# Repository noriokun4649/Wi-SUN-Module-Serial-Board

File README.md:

# Wi-SUN-Module-Serial-Board
秋月電子の謎SoCに内蔵されている Wi-SUN モジュール MB-RL7023-11 をUSBシリアルに変換する基板です。

# 基板画像

# 回路図

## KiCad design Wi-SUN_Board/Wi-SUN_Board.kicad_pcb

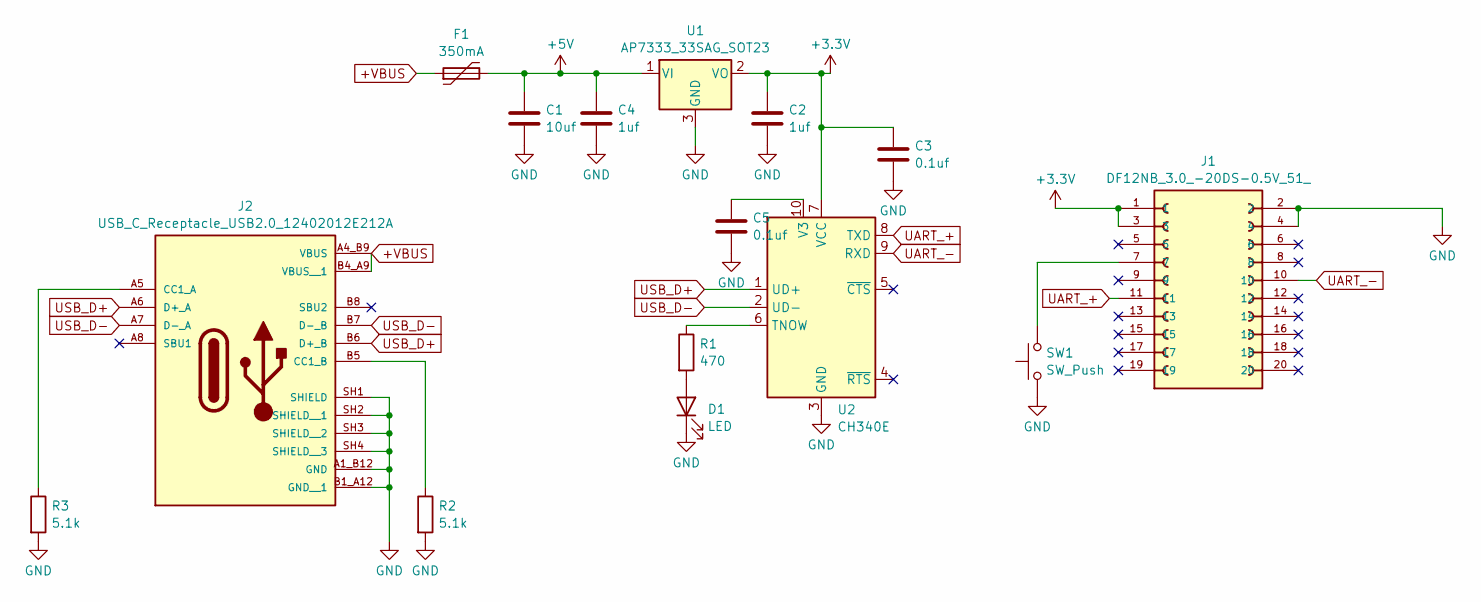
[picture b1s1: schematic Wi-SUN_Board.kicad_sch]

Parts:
C1: 10uf; C_0603_1608Metric_Pad1.08x0.95mm_HandSolder
C2, C4: 1uf; C_0402_1005Metric_Pad0.74x0.62mm_HandSolder
C3, C5: 0.1uf; C_0402_1005Metric_Pad0.74x0.62mm_HandSolder
D1: LED; LED_0603_1608Metric_Pad1.05x0.95mm_HandSolder
F1: 350mA; C_0603_1608Metric_Pad1.08x0.95mm_HandSolder
J1: DF12NB_3.0_-20DS-0.5V_51_; HRS_DF12NB_3.0_-20DS-0.5V_51_
J2: USB_C_Receptacle_USB2.0_12402012E212A; AMPHENOL_12402012E212A; PARTREV 4
R1: 470; R_0402_1005Metric_Pad0.72x0.64mm_HandSolder
R2, R3: 5.1k; R_0402_1005Metric_Pad0.72x0.64mm_HandSolder
SW1: SW_Push; TS-1187A-B-A-B
U1: AP7333_33SAG_SOT23; SOT-23
U2: CH340E; MSOP-10_3x3mm_P0.5mm

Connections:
+3.3V: C2.1, C3.1, J1.1, J1.3, U1.2 (VO), U2.7 (VCC)
+5V: C1.1, C4.1, F1.2, U1.1 (VI)
+VBUS: F1.1, J2.A4_B9 (VBUS), J2.B4_A9 (VBUS__1)
GND: C1.2, C2.2, C3.2, C4.2, C5.2, D1.1 (K), J1.2, J1.4, J2.A1_B12 (GND), J2.B1_A12 (GND__1), J2.SH1 (SHIELD), J2.SH2 (SHIELD__1), J2.SH3 (SHIELD__2), J2.SH4 (SHIELD__3), R2.2, R3.2, SW1.1, U1.3 (GND), U2.3 (GND)
unnamed: D1.2 (A), R1.2
unnamed: J1.7, SW1.2
unnamed: J2.A5 (CC1_A), R3.1
unnamed: J2.B5 (CC1_B), R2.1
unnamed: R1.1, U2.6 (TNOW)
unnamed: C5.1, U2.10 (V3)
UART_+: J1.11, U2.8 (TXD)
UART_-: J1.10, U2.9 (RXD)
USB_D+: J2.A6 (D+_A), J2.B6 (D+_B), U2.1 (UD+)
USB_D-: J2.A7 (D-_A), J2.B7 (D-_B), U2.2 (UD-)

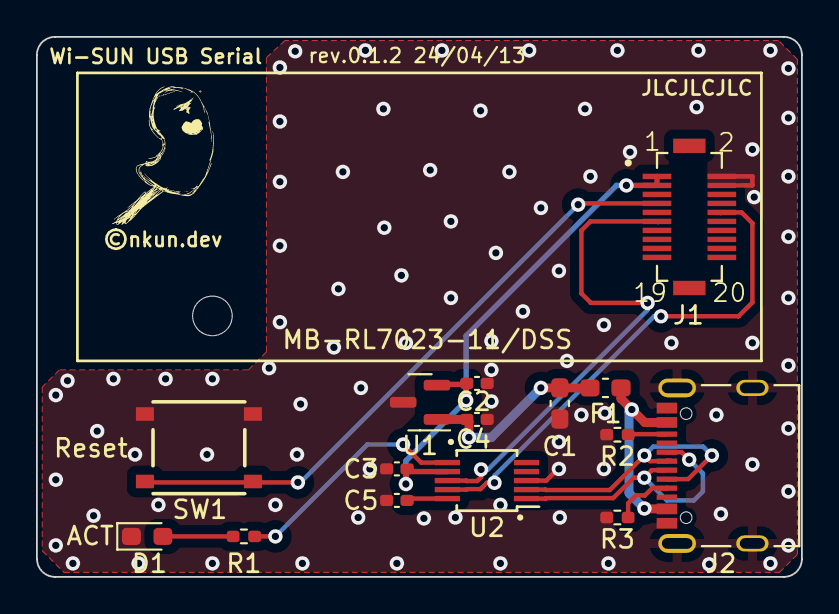
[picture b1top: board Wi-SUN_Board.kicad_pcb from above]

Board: 2 copper layers, 42.5 x 30.0 mm, 16 parts (0 on the bottom side), 14 nets.

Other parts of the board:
©nkun.dev: LOGO; logo_silk

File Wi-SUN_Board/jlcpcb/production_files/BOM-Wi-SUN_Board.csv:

Comment,Designator,Footprint,LCSC
350mA,F1,C_0603_1608Metric_Pad1.08x0.95mm_HandSolder,C116602
AP7333_33SAG_SOT23,U1,SOT-23,C150746
LED,D1,LED_0603_1608Metric_Pad1.05x0.95mm_HandSolder,C2290
470,R1,R_0402_1005Metric_Pad0.72x0.64mm_HandSolder,C25117
5.1k,"R2,R3",R_0402_1005Metric_Pad0.72x0.64mm_HandSolder,C25905
DF12NB_3.0_-20DS-0.5V_51_,J1,HRS_DF12NB_3.0_-20DS-0.5V_51_,C2917815
USB_C_Receptacle_USB2.0_12402012E212A,J2,USB_C_Receptacle_Amphenol_12402012E212A,C2988369
0.1uf,C3,C_0402_1005Metric_Pad0.74x0.62mm_HandSolder,C307331
SW_Push,SW1,TS-1187A-B-A-B,C318884
1uf,"C2,C4,C5",C_0402_1005Metric_Pad0.74x0.62mm_HandSolder,C52923
10uf,C1,C_0603_1608Metric_Pad1.08x0.95mm_HandSolder,C96446
CH340E,U2,MSOP-10_3x3mm_P0.5mm,C99652

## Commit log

2024-04-12 Init commit.
2024-04-15 フットプリントの細かい修正
